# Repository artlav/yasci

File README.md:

# Yet Another SCIntillation detector driver

A set of PCB designs to drive a PMT-based scintillation detector.  
Never got to finish it - the hardware is more or less done and largely tested, but failed to force myself to write the software/firmware.

## Power supply

 * A PMT needs around -1000V to work.
 * The logic stuff needs 5V.
 * The amplifier needs +5V and -5V.

This is a little brick that produces all of the above from 12V, using off-the-shelf converters to get +-5V and isolated 12V, boosting the isolated 12V to 250V, and voltage multiplying the 250V to 1000V.

## Amplifier

Takes the pulses from the PMT, amplifies and inverts them.  
I think i replaced MCP6021 with OPA172, for voltage limit reasons.

## ADC

An FPGA module with an ADC attached to it.  
Takes the analog output of the amplifier, digitizes it, processes/detects peaks, and saves it on a microsd card.  
The sync output is there to synchronize timings between several boards, i.e. for muon detection.

## Blank / FEU-85 / FEU-35

PMT boards, with amplifier mount point and resistor divider ladder.  
Pinouts for common ФЭУ-85 and ФЭУ-35 PMT tubes, as well as a blank one intended for an already-populated PMT module.

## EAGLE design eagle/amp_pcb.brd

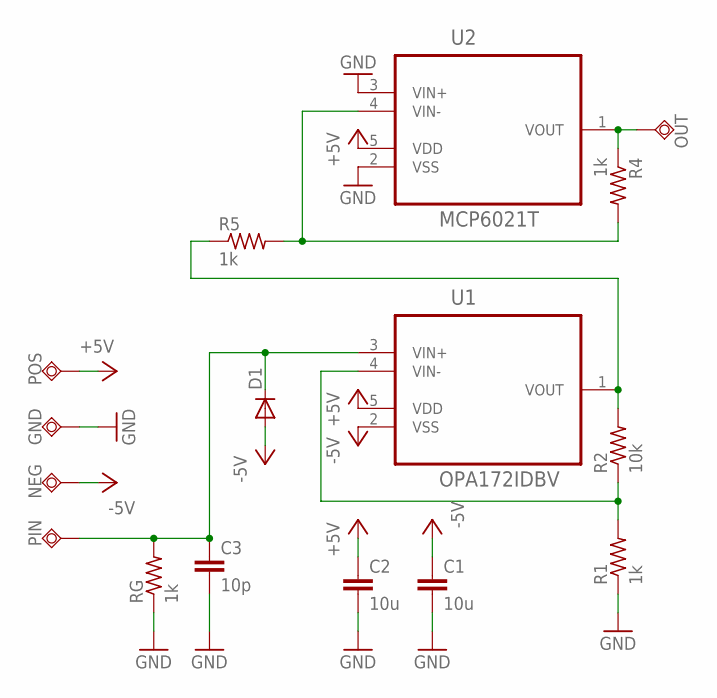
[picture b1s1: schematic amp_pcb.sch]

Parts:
C1, C2: 10u; C0603
C3: 10p; C0603
D1: DIODE-DO214AA; DO214AA
GND: TPSQTP15SQ; TP15SQ
NEG: TPSQTP15SQ; TP15SQ
OUT: TPSQTP15SQ; TP15SQ
PIN: TPSQTP15SQ; TP15SQ
POS: TPSQTP15SQ; TP15SQ
R1, R4, R5: 1k; R0603
R2: 10k; R0603
RG: 1k; R0603
U1: OPA172IDBV; SOT95P320X145-5N
U2: MCP6021T; SOT95P320X145-5N

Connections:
+5V: C2.1, POS.TP, U1.5 (VDD), U2.5 (VDD)
-5V: C1.1, D1.A, NEG.TP, U1.2 (VSS)
GND: C1.2, C2.2, C3.2, GND.TP, R1.1, RG.1, U2.2 (VSS), U2.3 (VIN+)
unnamed: R1.2, R2.1, U1.4 (VIN-)
unnamed: R2.2, R5.1, U1.1 (VOUT)
unnamed: C3.1, D1.C, PIN.TP, RG.2, U1.3 (VIN+)
unnamed: OUT.TP, R4.1, U2.1 (VOUT)
unnamed: R4.2, R5.2, U2.4 (VIN-)

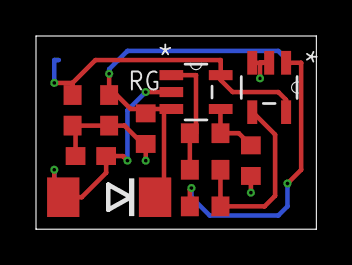
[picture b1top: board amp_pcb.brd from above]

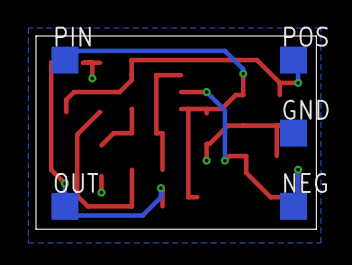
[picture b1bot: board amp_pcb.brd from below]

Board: 2 copper layers, 15.6 x 10.7 mm, 16 parts (5 on the bottom side), 8 nets.

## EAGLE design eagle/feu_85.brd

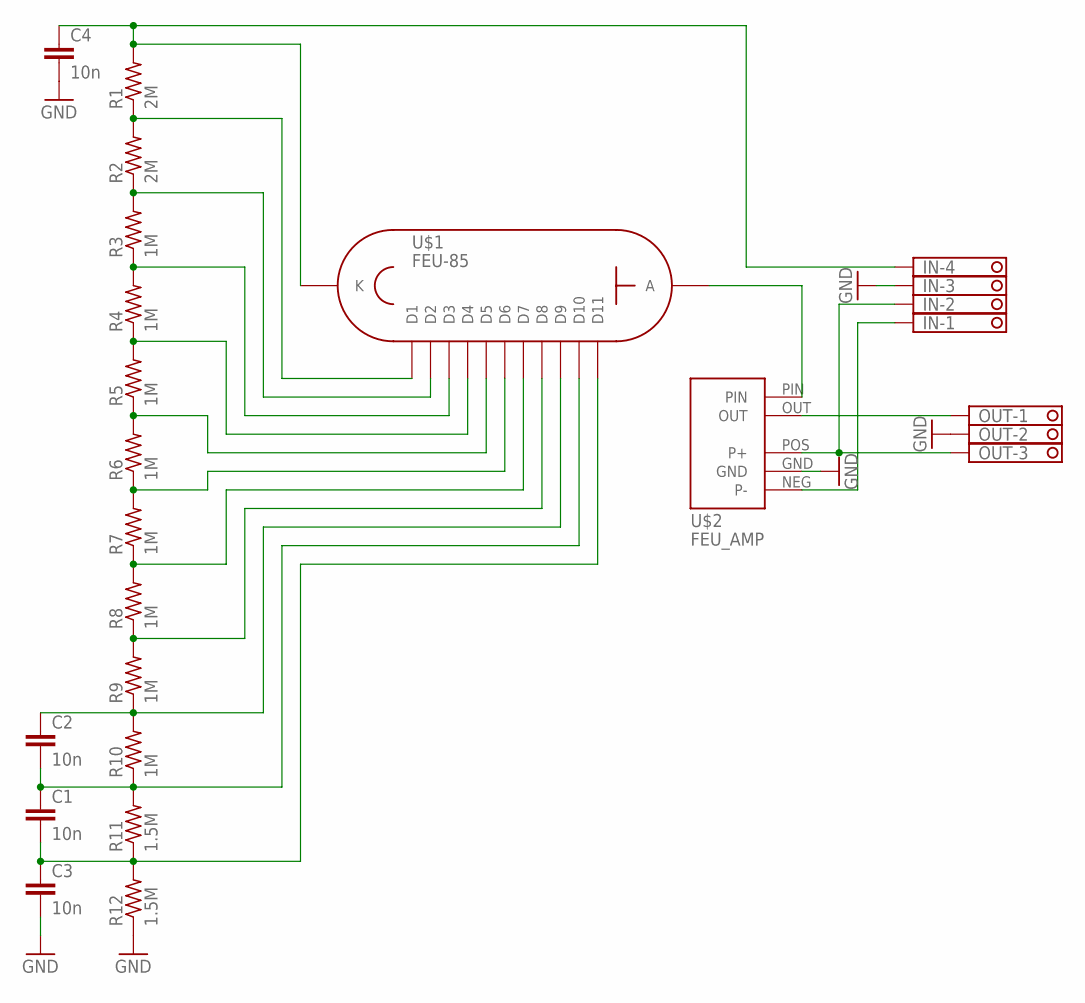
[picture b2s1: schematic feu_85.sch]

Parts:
C1, C2, C3: 10n; C075-032X103
C4: 10n; C225-087X268
IN: 1751264
OUT: 1751251
R1, R2: 2M; 0207/2V
R3, R4, R5, R6, R7, R8, R9, R10: 1M; 0207/2V
R11, R12: 1.5M; 0207/2V
U$1: FEU-85; PANEL_14
U$2: FEU_AMP

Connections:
GND: C3.2, C4.2, IN.3, OUT.2, R12.1, U$2.GND
unnamed: R1.1, R2.2, U$1.P$13 (D1)
unnamed: R3.1, R4.2, U$1.P$12 (D3)
unnamed: R4.1, R5.2, U$1.P$3 (D4)
unnamed: R5.1, R6.2, U$1.P$11 (D5)
unnamed: R6.1, R7.2, U$1.P$4 (D6)
unnamed: R7.1, R8.2, U$1.P$10 (D7)
unnamed: R8.1, R9.2, U$1.P$5 (D8)
unnamed: C2.1, R9.1, R10.2, U$1.P$9 (D9)
unnamed: OUT.1, U$2.OUT
unnamed: IN.2, OUT.3, U$2.POS (P+)
unnamed: R2.1, R3.2, U$1.P$2 (D2)
unnamed: C4.1, IN.4, R1.2, U$1.P$14 (K)
unnamed: C1.2, C3.1, R11.1, R12.2, U$1.P$8 (D11)
unnamed: C1.1, C2.2, R10.1, R11.2, U$1.P$6 (D10)
unnamed: U$1.P$7 (A), U$2.PIN
unnamed: IN.1, U$2.NEG (P-)

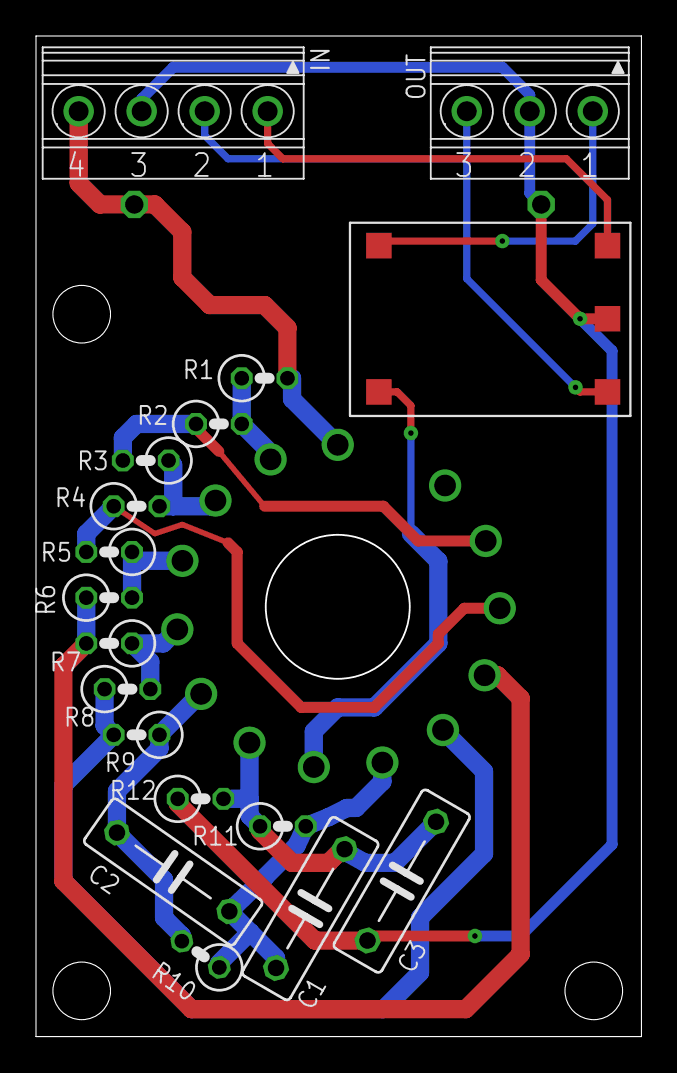
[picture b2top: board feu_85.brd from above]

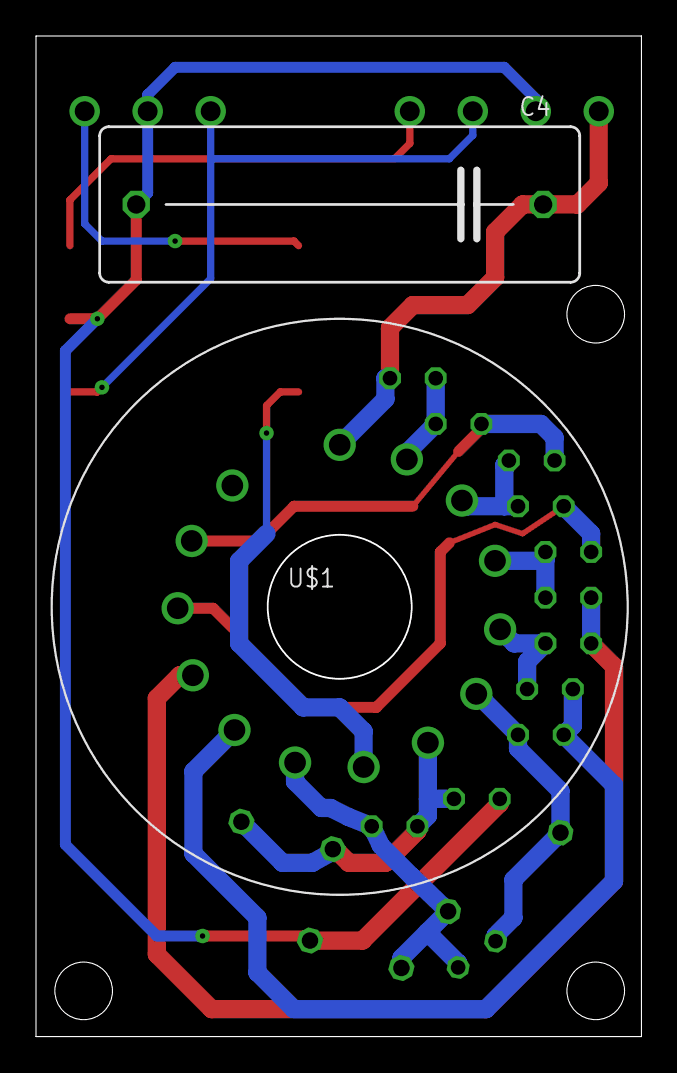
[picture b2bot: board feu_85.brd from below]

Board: 2 copper layers, 33.5 x 55.5 mm, 20 parts (2 on the bottom side), 17 nets.

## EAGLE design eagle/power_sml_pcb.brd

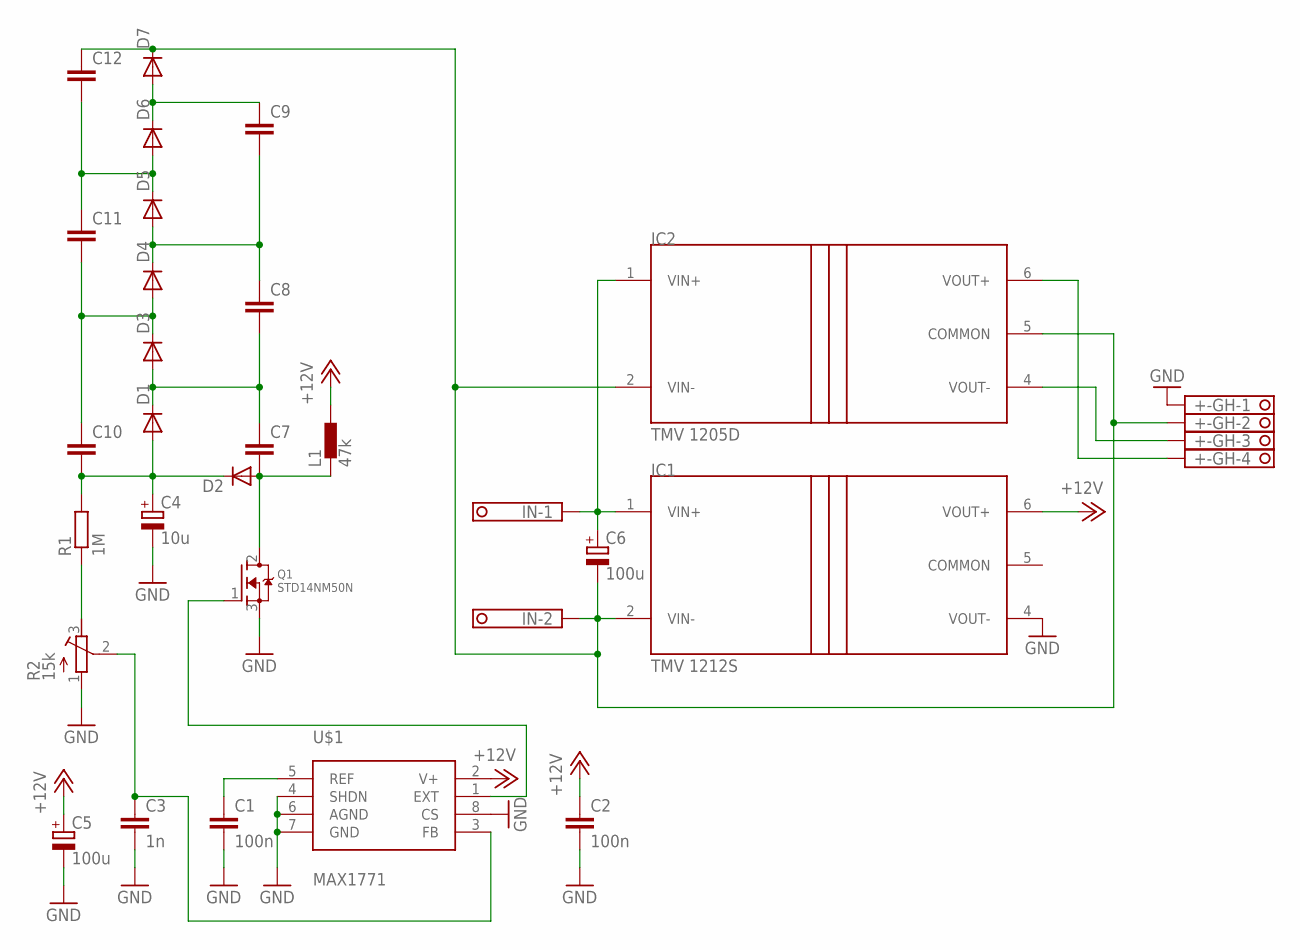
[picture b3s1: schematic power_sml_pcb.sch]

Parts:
+-GH: 1751264
C1, C2: 100n; C0603
C3: 1n; C0603
C4: 10u; E5-10,5
C5: 100u; SMC_C
C6: 100u; E2,5-6
C7, C8, C9, C10, C11, C12: C-EU102-054X133; C102-054X133
D1, D2, D3, D4, D5, D6, D7: DIODE-DO214AA; DO214AA
IC1: TMV 1212S; SIP7
IC2: TMV 1205D; SIP7
IN: 1751248
L1: 47k; DR1030
Q1: STD14NM50N; DPAK
R1: 1M; 0207/7
R2: 15k; RTRIM3296W
U$1: MAX1771; SOIC8

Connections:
+12V: C2.1, C5.+, IC1.6 (VOUT+), L1.2, U$1.2 (V+)
COMMON: IC1.5 (COMMON)
GND: +-GH.1, C1.2, C2.2, C3.2, C4.-, C5.-, IC1.4 (VOUT-), Q1.3 (S), R2.1 (E), U$1.4 (SHDN), U$1.6 (AGND), U$1.7 (GND), U$1.8 (CS)
unnamed: C1.1, U$1.5 (REF)
unnamed: C3.1, R2.2 (S), U$1.3 (FB)
unnamed: Q1.1 (G), U$1.1 (EXT)
unnamed: C7.2, D2.A, L1.1, Q1.2 (D)
unnamed: C4.+, C10.2, D1.A, D2.C, R1.2
unnamed: R1.1, R2.3 (A)
unnamed: C6.+, IC1.1 (VIN+), IC2.1 (VIN+), IN.1
unnamed: +-GH.4, IC2.6 (VOUT+)
unnamed: +-GH.3, IC2.4 (VOUT-)
unnamed: +-GH.2, C6.-, C12.1, D7.C, IC1.2 (VIN-), IC2.2 (VIN-), IC2.5 (COMMON), IN.2
unnamed: C7.1, C8.2, D1.C, D3.A
unnamed: C10.1, C11.2, D3.C, D4.A
unnamed: C8.1, C9.2, D4.C, D5.A
unnamed: C11.1, C12.2, D5.C, D6.A
unnamed: C9.1, D6.C, D7.A

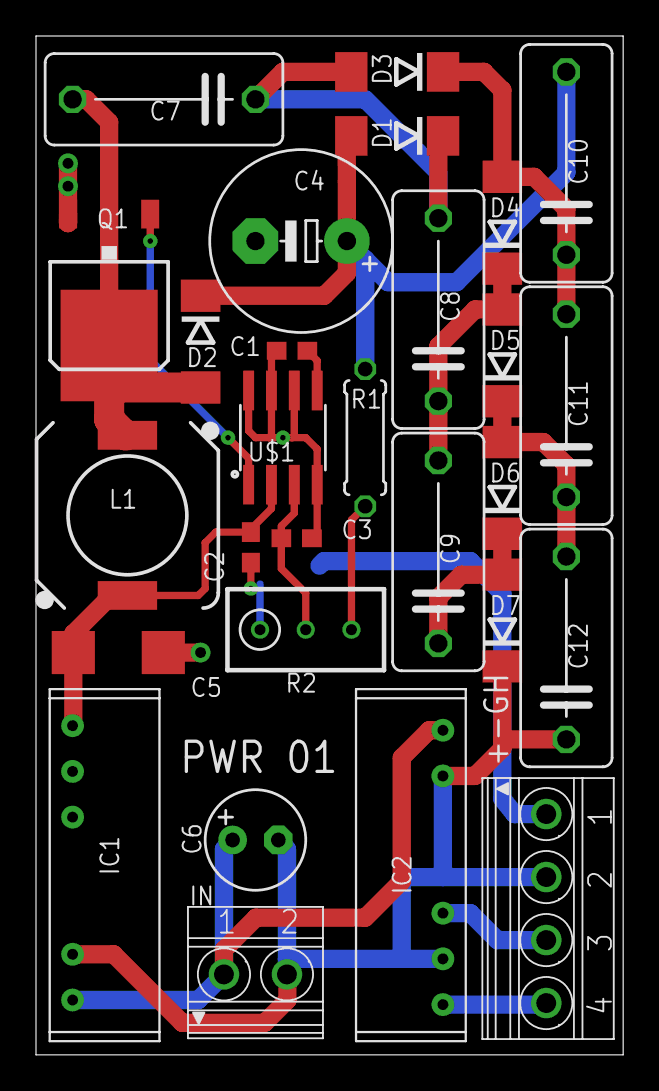
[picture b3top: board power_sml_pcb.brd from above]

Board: 2 copper layers, 32.6 x 56.6 mm, 28 parts (0 on the bottom side), 17 nets.

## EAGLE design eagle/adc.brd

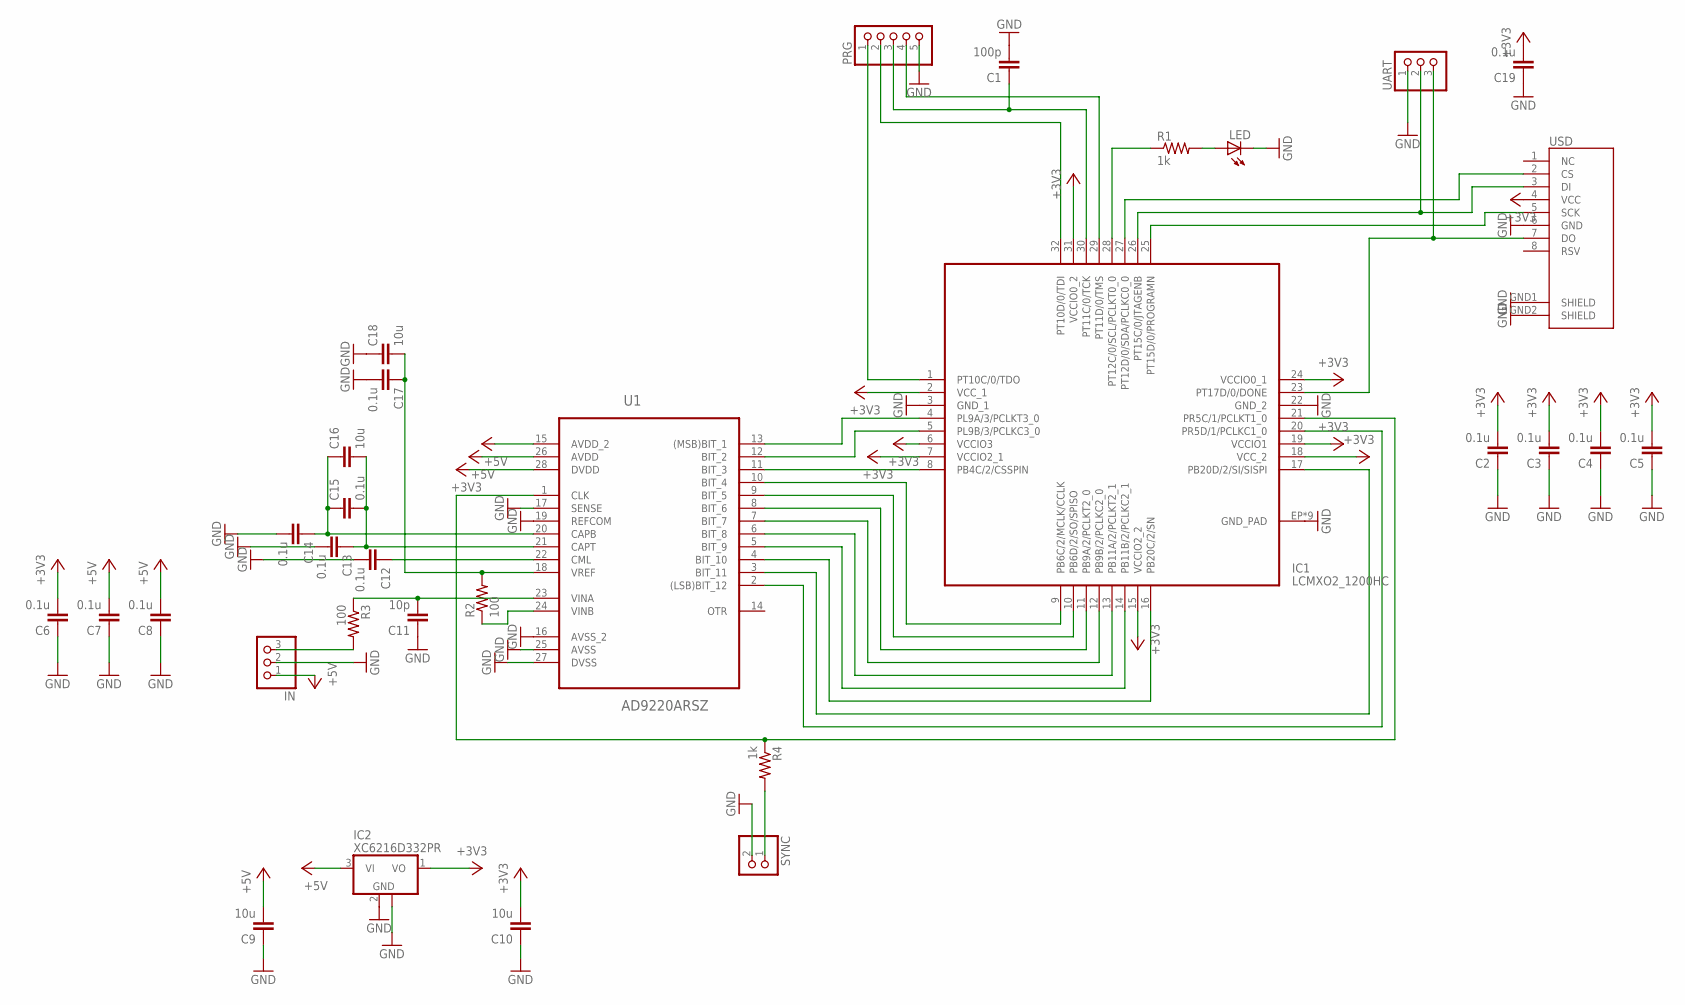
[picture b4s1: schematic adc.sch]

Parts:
C1: 100p; C0603
C2, C3, C4, C5, C6, C7, C8, C12, C13, C14, C15, C17, C19: 0.1u; C0603
C9, C10, C16, C18: 10u; C1206
C11: 10p; C0603
IC1: LCMXO2_1200HC; QFN32_5X5
IC2: XC6216D332PR; SOT89
IN: PINHD-1X3; 1X03
LED: LEDSML0805; SML0805
PRG: PINHD-1X5; 1X05
R1, R4: 1k; R0603
R2, R3: 100; R0603
SYNC: PINHD-1X2; 1X02
U1: AD9220ARSZ; SOP65P780X200-28N
UART: PINHD-1X3; 1X03
USD: USD-SOCKETUSD; USD-SOCKET-PP

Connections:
+3V3: C2.2, C3.2, C4.2, C5.2, C6.2, C10.2, C19.2, IC1.2 (VCC_1), IC1.6 (VCCIO3), IC1.7 (VCCIO2_1), IC1.15 (VCCIO2_2), IC1.18 (VCC_2), IC1.19 (VCCIO1), IC1.24 (VCCIO0_1), IC1.31 (VCCIO0_2), IC2.1 (VO), U1.28 (DVDD), USD.4 (VCC)
+5V: C7.2, C8.2, C9.2, IC2.3 (VI), IN.1, U1.15 (AVDD_2), U1.26 (AVDD)
GND: C1.2, C2.1, C3.1, C4.1, C5.1, C6.1, C7.1, C8.1, C9.1, C10.1, C11.1, C12.2, C13.2, C14.2, C17.2, C18.1, C19.1, IC1.3 (GND_1), IC1.22 (GND_2), IC1.EP (GND_PAD), IC1.EP1 (GND_PAD), IC1.EP2 (GND_PAD), IC1.EP3 (GND_PAD), IC1.EP4 (GND_PAD), IC1.EP5 (GND_PAD), IC1.EP6 (GND_PAD), IC1.EP7 (GND_PAD), IC1.PAD (GND_PAD), IC2.2 (GND), IC2.2@1 (GND), IN.2, LED.C, PRG.5, SYNC.2, U1.16 (AVSS_2), U1.17 (SENSE), U1.19 (REFCOM), U1.25 (AVSS), U1.27 (DVSS), UART.1, USD.6 (GND), USD.GND1 (SHIELD), USD.GND2 (SHIELD)
unnamed: IC1.4 (PL9A/3/PCLKT3_0), U1.13 ((MSB)BIT_1)
unnamed: IC1.5 (PL9B/3/PCLKC3_0), U1.12 (BIT_2)
unnamed: IC1.8 (PB4C/2/CSSPIN), U1.11 (BIT_3)
unnamed: IC1.9 (PB6C/2/MCLK/CCLK), U1.10 (BIT_4)
unnamed: IC1.10 (PB6D/2/SO/SPISO), U1.9 (BIT_5)
unnamed: IC1.11 (PB9A/2/PCLKT2_0), U1.8 (BIT_6)
unnamed: IC1.12 (PB9B/2/PCLKC2_0), U1.7 (BIT_7)
unnamed: IC1.13 (PB11A/2/PCLKT2_1), U1.6 (BIT_8)
unnamed: IC1.14 (PB11B/2/PCLKC2_1), U1.5 (BIT_9)
unnamed: IC1.16 (PB20C/2/SN), U1.4 (BIT_10)
unnamed: IC1.17 (PB20D/2/SI/SISPI), U1.3 (BIT_11)
unnamed: IC1.20 (PR5D/1/PCLKC1_0), U1.2 ((LSB)BIT_12)
unnamed: IC1.21 (PR5C/1/PCLKT1_0), R4.1, U1.1 (CLK)
unnamed: IC1.1 (PT10C/0/TDO), PRG.1
unnamed: IC1.32 (PT10D/0/TDI), PRG.2
unnamed: C1.1, IC1.30 (PT11C/0/TCK), PRG.3
unnamed: IC1.29 (PT11D/0/TMS), PRG.4
unnamed: IC1.23 (PT17D/0/DONE), UART.3, USD.7 (DO)
unnamed: IC1.25 (PT15D/0/PROGRAMN), USD.5 (SCK)
unnamed: IC1.26 (PT15C/0/JTAGENB), UART.2, USD.3 (DI)
unnamed: IC1.27 (PT12D/0/SDA/PCLKC0_0), USD.2 (CS)
unnamed: IC1.28 (PT12C/0/SCL/PCLKT0_0), R1.1
unnamed: LED.A, R1.2
unnamed: R2.1, U1.24 (VINB)
unnamed: C17.1, C18.2, R2.2, U1.18 (VREF)
unnamed: C11.2, R3.1, U1.23 (VINA)
unnamed: IN.3, R3.2
unnamed: C12.1, U1.22 (CML)
unnamed: C13.1, C15.2, C16.2, U1.21 (CAPT)
unnamed: C14.1, C15.1, C16.1, U1.20 (CAPB)
unnamed: R4.2, SYNC.1

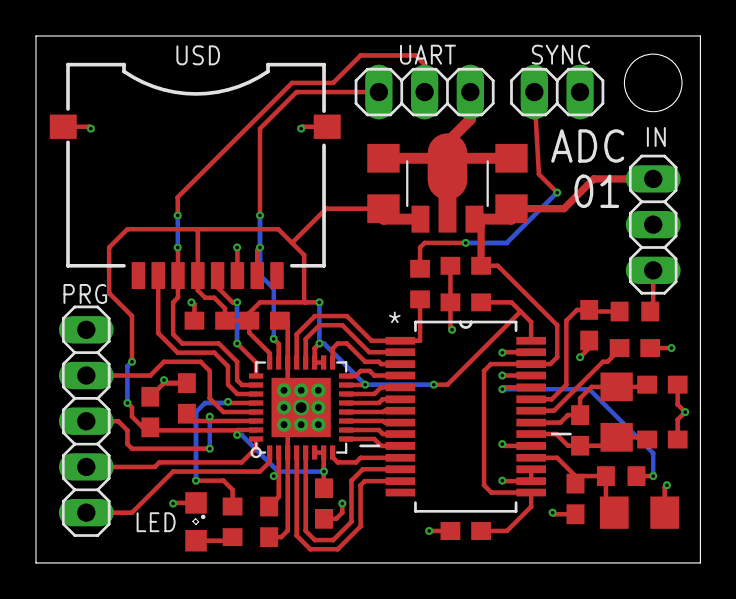
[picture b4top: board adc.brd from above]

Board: 2 copper layers, 36.9 x 29.3 mm, 32 parts (0 on the bottom side), 34 nets.

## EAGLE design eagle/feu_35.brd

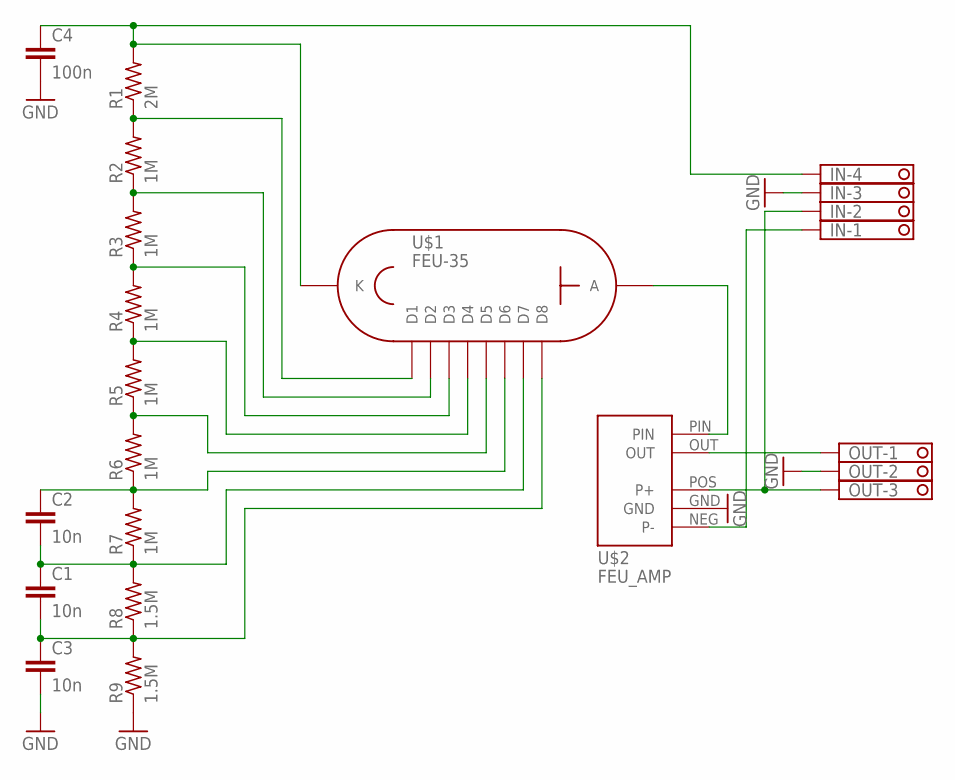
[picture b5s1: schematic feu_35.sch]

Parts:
C1, C2, C3: 10n; C075-032X103
C4: 100n; C225-087X268
IN: 1751264
OUT: 1751251
R1: 2M; 0207/2V
R2, R3, R4, R5, R6, R7: 1M; 0207/2V
R8, R9: 1.5M; 0207/2V
U$1: FEU-35; PANEL_10
U$2: FEU_AMP

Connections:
GND: C3.2, C4.2, IN.3, OUT.2, R9.1, U$2.GND
unnamed: R1.1, R2.2, U$1.P$2 (D1)
unnamed: R3.1, R4.2, U$1.P$4 (D3)
unnamed: R4.1, R5.2, U$1.P$5 (D4)
unnamed: R5.1, R6.2, U$1.P$6 (D5)
unnamed: C2.1, R6.1, R7.2, U$1.P$7 (D6)
unnamed: U$1.P$10 (A), U$2.PIN
unnamed: OUT.1, U$2.OUT
unnamed: IN.2, OUT.3, U$2.POS (P+)
unnamed: IN.1, U$2.NEG (P-)
unnamed: R2.1, R3.2, U$1.P$3 (D2)
unnamed: C4.1, IN.4, R1.2, U$1.P$1 (K)
unnamed: C1.2, C3.1, R8.1, R9.2, U$1.P$9 (D8)
unnamed: C1.1, C2.2, R7.1, R8.2, U$1.P$8 (D7)

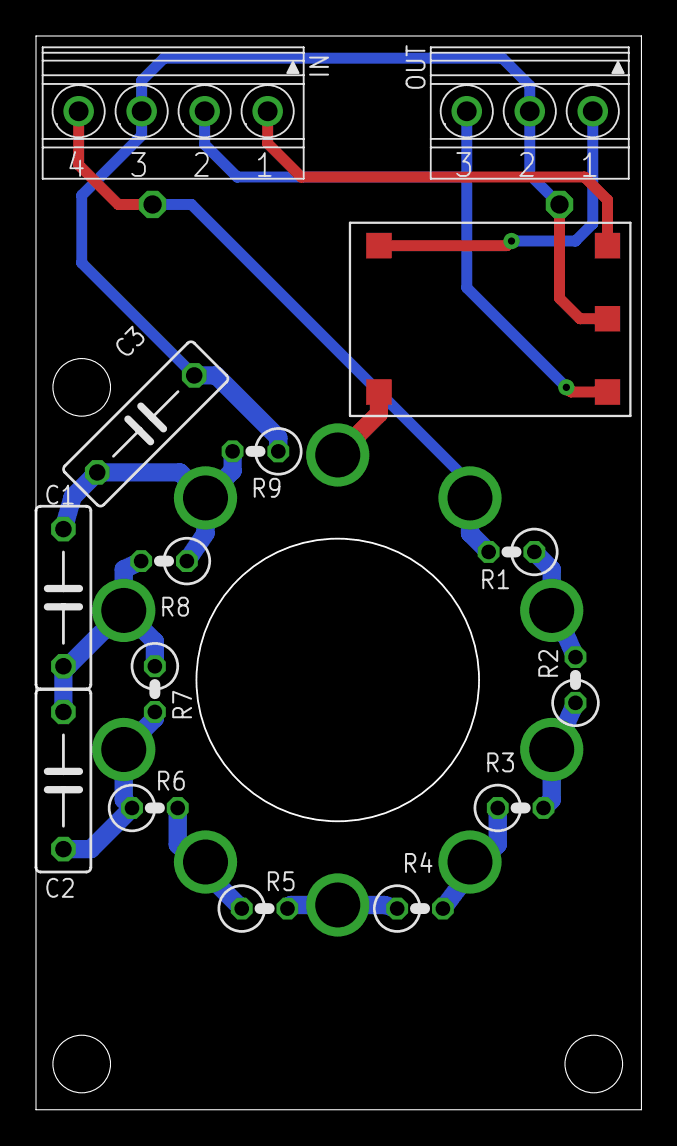
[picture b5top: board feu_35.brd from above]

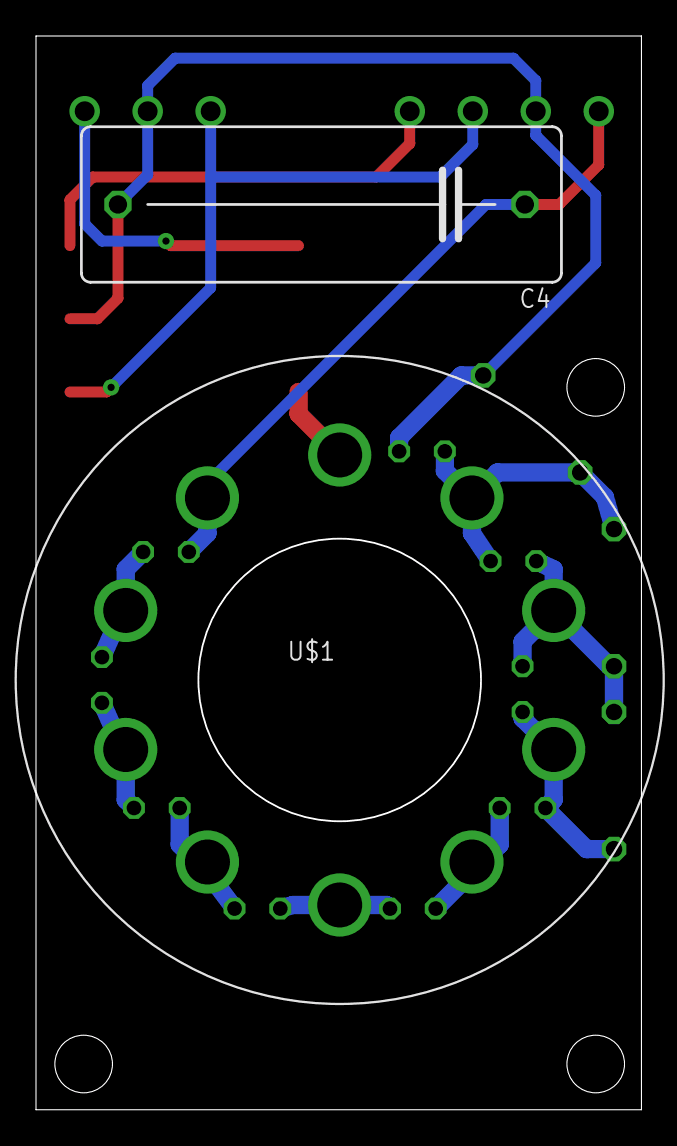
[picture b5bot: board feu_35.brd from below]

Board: 2 copper layers, 33.5 x 59.6 mm, 17 parts (2 on the bottom side), 14 nets.

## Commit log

2020-08-27 Initial upload
